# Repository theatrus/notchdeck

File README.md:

# NotchDeck

**NotchDeck One** is a BenchBits train controller project with USB HID and Bluetooth LE HID.
It supports our own Japanese-style **separate power lever and rotary brake**, or a
**combined mascon**. Each handle can use an AS5600 magnetic sensor or a Gray-code
contact cam. The goal is a driverless joystick with host-controlled lighting;
host/game compatibility has not yet been bench-tested.

## Current design: Rev G logic + Rev E button panel

| Assembly | Function | Provisional floorplan |
|---|---|---|
| [Logic / connectors](hardware/notchdeck-one/FLOORPLAN.md) | E73 nRF52840 module, USB/BLE, battery power, handle ports, Select/Start, two solenoids and buzzer | 115×90mm, four layers |
| [Button panel](hardware/notchdeck-buttons/README.md) | STM32G030, detachable 4×4 diode key matrix, 16 RGB LEDs | 86×120mm, two layers, 19mm key pitch |

A six-way 1mm FFC carries power, I²C and interrupt between boards. The selected cable
is Molex **0151670213** (DigiKey **WM13121-ND**); the panel guide records its reversed
connector numbering and remaining fit checks. The STM32G030 **C529330** was selected
from owned JLCPCB inventory.

The [actuator sheet](hardware/notchdeck-one/ACTUATORS.md) adds two PWM low-side
outputs, an active-buzzer output and 3.3V signals for an external 12V driver.
A TPS259461LRPWR electronic limiter protects the full battery input at 5.05A
nominal. The provisional target is two simultaneous 2A strikes of up to 100ms,
then lower PWM hold current. Use a protected ≥6A 1S pack for upstream shorts.
ACT_EN pauses charging during actuation; the PWM inputs default off.

Both hierarchical schematics are wired and pass strict ERC, complete net checks,
schematic/PCB parity and BOM audits. **Both PCBs are unrouted floorplans and are not
ready for fabrication.** The [hardware guide](hardware/README.md) tracks routing,
mechanical, power-budget and assembly work still required.

The nRF firmware builds against NCS v3.3.0, with host tests and six Rev C/D handle
profiles compiled in CI. **Panel firmware, main-board I²C integration and Rev G actuator control are
not implemented.** Keep loads disconnected when using old Rev C/D firmware.
Magnetic handles also require measured detent calibration. No production firmware,
bootloader integration or fabricated-controller validation is claimed.

## Handles and reports

Combined mode sends discrete notch values on HID **Y**: EB=`0x00`, N=`0x80`, P5=`0xFF`.
Separate-handle mode uses **Y=power, X=brake**, with brake priority and neutral
re-arming. Both magnetic and contact backends use absolute positions. See the
[handle interface](docs/06-handle-interfaces.md) for cam codes, calibration and
profiles, and the [own-build guide](docs/07-japanese-handle-build.md) for mechanisms
and the provisional panel layout.

## Checks and exports

Run from the repository root:

```sh
make -C firmware test             # host compiler only
make -C hardware verify           # KiCad 10 + Python with pcbnew
make -C hardware jlc              # separate logic and button assembly ZIPs
```

On Linux, pass `KICAD_PYTHON=python3` to hardware checks with KiCad's Python module
installed. The [hardware guide](hardware/README.md) covers setup and regeneration;
the [firmware guide](firmware/README.md) covers NCS builds and release commands.

Each hardware ZIP contains Gerbers, drill, BOM and pick-and-place (CPL) files.
Exports describe the current unfinished boards; exporting does not approve them
for manufacture. [Sourcing](docs/04-bom-sourcing.md) covers **five complete sets**:
213 installed parts and 44 JLCPCB codes per set, plus the separate cable. Stock
observations are dated snapshots, with private inventory retained outside Git.
The earlier Rev E parts order was placed; the Rev G actuator expansion still
needs a top-up for 20 sets plus 10% spares. See the sourcing guide.

[GitHub Actions](https://github.com/theatrus/notchdeck/actions/workflows/ci.yml)
publishes `notchdeck-boms` (both assembly BOMs) and `notchdeck-one-firmware`
(default nRF52840 DK bring-up UF2/HEX). Handle profiles are compile checks only;
there is no Rev E/F or STM32 image in those artifacts. CI checks floorplan DRC rules
and parity while allowing the documented unrouted connections.

## Documentation

| Guide | Contents |
|---|---|
| [Hardware](hardware/README.md) | KiCad projects, validation, manufacturing exports and open work |
| [Actuators](hardware/notchdeck-one/ACTUATORS.md) | Short protection, connectors, PWM limits and required firmware |
| [Firmware](firmware/README.md) | Build/test commands, CI artifacts and implementation status |
| [Architecture](docs/03-hardware-and-firmware-architecture.md) | Two-board design, buses, power and firmware responsibilities |
| [Sourcing](docs/04-bom-sourcing.md) | Assembly BOMs, five-set stock accounting and external parts |
| [Parts](hardware/PARTS.md) / [net plan](hardware/NETPLAN.md) | Exact selections, footprints, pad assignments and wiring |
| [Handle interfaces](docs/06-handle-interfaces.md) | Magnetic/Gray harnesses, codes, profiles and fault behavior |
| [Japanese-style handle build](docs/07-japanese-handle-build.md) | Own-build mechanics, provisional layout and cam targets |
| [Protocol](docs/02-emulation-protocol-spec.md) | HID reports, notch encoding and planned lighting features |
| [Firmware updates](docs/05-firmware-update.md) | Current artifacts, SWD access and proposed user-update path |
| [Research](docs/01-research-findings.md) | Original Zuiki/Densha de GO! protocol research and references |

## License

TBD; a project-wide license has not yet been selected. Third-party library sources
and licenses are recorded in [attributions](hardware/lib/ATTRIBUTIONS.md).

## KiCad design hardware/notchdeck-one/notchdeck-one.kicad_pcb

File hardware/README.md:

# NotchDeck hardware

**Rev G logic and Rev E panel are two wired KiCad 10 assemblies:** `notchdeck-one` is the logic/handle board; `notchdeck-buttons` is the detachable 4×4 key/RGB board. The button board uses an owned **STM32G030F6P6TR / C529330** to scan a diode matrix and drive RGB locally. A six-way 1mm FFC carries I²C, interrupt and power. Select/Start remain direct inputs on the main board, alongside Reset.

| Project | Provisional PCB | Electrical components | Nets / endpoints | Assembly parts |
|---|---|---:|---|---:|
| [Logic](notchdeck-one/FLOORPLAN.md) | 115×90mm, four layers | 130 | 94 / 409 | 129 |
| [Buttons](notchdeck-buttons/README.md) | 86×120mm, two layers; 19mm key pitch | 85 | 56 / 235 | 84 |

Both have zero native ERC errors/warnings, complete independent net contracts, and matching PCB pad nets, schematic UUIDs and sourcing properties. Both are **unrouted floorplans**, with no tracks/vias/planes. Native DRC has no rule or schematic-parity violations; 323 logic and 211 button connections remain unrouted. Neither is ready to fabricate.

Open `notchdeck-one/notchdeck-one.kicad_pro` and
`notchdeck-buttons/notchdeck-buttons.kicad_pro` in KiCad 10 to inspect the complete
projects, then open each project's root schematic or PCB from its project manager.
The root schematics link the child sheets; symbols/footprints use standard KiCad
libraries plus the shared project-local `lib/` directory.

Magnetic and Gray-coded power/brake or combined mascon interfaces remain electrically unchanged. See [handle interfaces](../docs/06-handle-interfaces.md). U9 separates the two AS5600 address-0x36 channels; MAX17048 remains on another bus. Remove both R37/R38 before using an external power/combined sensor on J10.

Rev G adds [two solenoids, an active buzzer and external PWM](notchdeck-one/ACTUATORS.md). The actuator feed uses electronic current limiting, with no disposable fuse. A protected ≥6A 1S pack is mandatory for upstream battery-lead/PCB shorts. Full battery input protection is set to 5.05A nominal, with a 4.3A operating budget and two provisional 2A/100ms strikes. ACT_EN pauses charging; PWM pulldowns default the loads off.

## Source of truth and build

Edit `scripts/<project>.schgen.py` and each project's `bom/jlcpcb-parts.json`, then generate with the schematic editors closed. `notchdeck_capture.py` supplies shared wire/port capture; `kschgen.py` handles native files. Keep editor changes in those manifests before forcing regeneration. The saved PCBs become the source of truth once placement/routing proceeds; the seed floorplan script refuses to overwrite routed boards.

```sh
# From hardware/; <project> is notchdeck-one or notchdeck-buttons.
KSCHGEN_FORCE=1 make gen-notchdeck-one gen-notchdeck-buttons
make verify                     # both boards: net/ERC, PCB parity and BOM audits
make render-notchdeck-one render-notchdeck-buttons
make docs                       # both boards' images and BOMs
make jlc                        # two separate Gerber/drill/BOM/CPL ZIPs
make jlc-notchdeck-buttons       # or export one PCB
```

Pick-and-place files are `<project>/jlcpcb/<project>-CPL.csv`; ZIPs are `<project>/<project>-jlcpcb.zip`. These commands export the current design, including unfinished floorplans; they do not constitute a manufacturing release. Review rotations in JLCPCB before ordering. Generated exports are ignored by Git. CI audits both projects; on Linux pass `KICAD_PYTHON=python3` with `pcbnew` installed. See [script guide](scripts/README.md).

Use `KICAD_CLI=/Applications/KiCad/KiCad.app/Contents/MacOS/kicad-cli` on macOS
if the executable is not on PATH; the Makefile's native export targets need it.
The default `KICAD_PYTHON` points to KiCad's bundled macOS Python. Headless Linux
also needs the standard symbol/footprint tables installed, as shown in
[CI setup](../.github/workflows/ci.yml). Rendering PNG sheets requires an SVG
converter listed in the script guide.

CI publishes both generated BOM CSVs as `notchdeck-boms`; it does not publish
assembly ZIPs or CPLs. `make verify` does not include native DRC: CI runs that
separately, rejects rule/parity violations and reports unrouted counts. Before
manufacturing, all unintended unconnected items must also be resolved.

## Sourcing and remaining work

[PARTS.md](PARTS.md) maps all **213 installed parts / 44 JLCPCB codes** per set. [Five-set stock](jlcpcb-five-set-stock.csv) combines both boards’ usage: dated public availability or owned stock covers the five-set requirement; new C3662776 has 110 displayed in stock, with order allocation still to confirm. Private inventory balances remain outside Git. [System BOM](system-bom.csv) adds one DigiKey Molex 0151670213 cable per set. The user placed the earlier Rev E parts order; the shared CSV was refreshed afterward. Rev G additions need a separate top-up, recorded locally in `~/Dropbox-elec/github/notchdeck-actuator-expansion-2026-10-04.csv`. Stock observations do not reserve parts. Handle mechanisms, external sensor carriers, cell, keycaps and enclosure are not yet a sourced kit.

- Implement panel MCU firmware and main I²C integration. Existing Rev C/D direct-GPIO button/RGB firmware does **not** operate this Rev E panel. The [panel guide](notchdeck-buttons/README.md) records pin functions, scan behavior, address and programming requirements.
- Implement Rev G actuator startup/strike/hold, instantaneous current-budget scheduling, undervoltage shutdown, fault latching and timeout handling. No safe actuator image exists yet. Select actual coils/buzzer and a protected pack; qualify short behavior and temperature rise.
- Finalize enclosure, cable fit/retention and tolerances, mounting and connector access. The FFC is nominally compatible; its guaranteed thickness tolerance is wider than the connector drawing. Sample-fit or supplier approval remains required.
- Validate E73 land pattern/antenna region and MAX17048 exposed pad. Review final CPL orientation and assembly eligibility.
- Resolve USB source/current/inrush and the existing 500mA charger setting. RGB is USB-only; a ≤250mA total panel return target is below the 0.5A FFC-contact rating, but still needs firmware enforcement and a whole-system power budget. Review LDO margins and battery choice.
- Finish decoupling placement, USB/ESD routing, reference planes and ground stitching; route and run final DRC/DFM/EMC checks. Magnetic detents need measured calibration; handle hardware and power/thermal behavior need bench testing.

Connectivity and catalog checks establish internal consistency, not complete electrical, mechanical or production validation. No ERC exclusions were added.

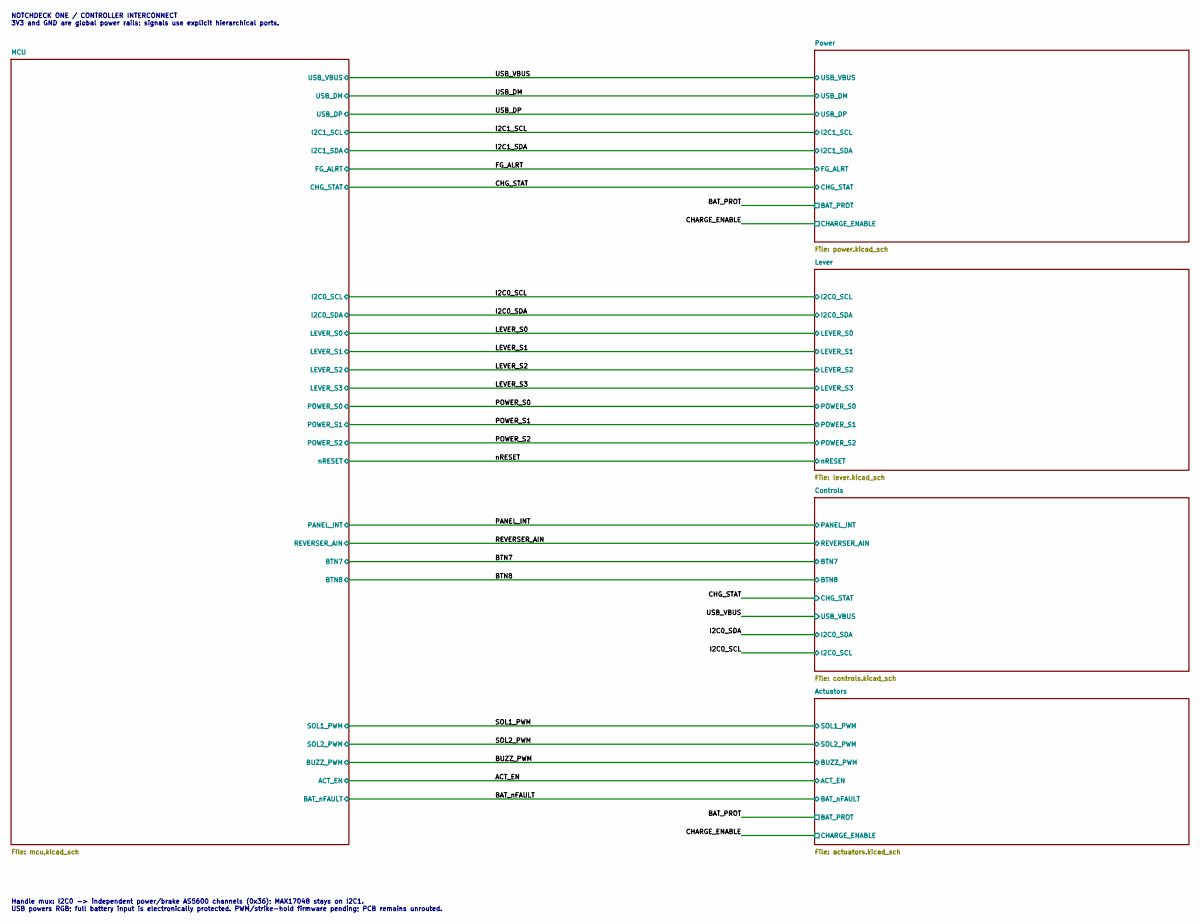
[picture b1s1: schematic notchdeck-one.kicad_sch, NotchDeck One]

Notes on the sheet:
NOTCHDECK ONE / CONTROLLER INTERCONNECT 3V3 and GND are global power rails; signals use explicit hierarchical ports.
Handle mux: I2C0 -> independent power/brake AS5600 channels (0x36); MAX17048 stays on I2C1. USB powers RGB; full battery input is electronically protected. PWM/strike-hold firmware pending; PCB remains unrouted.

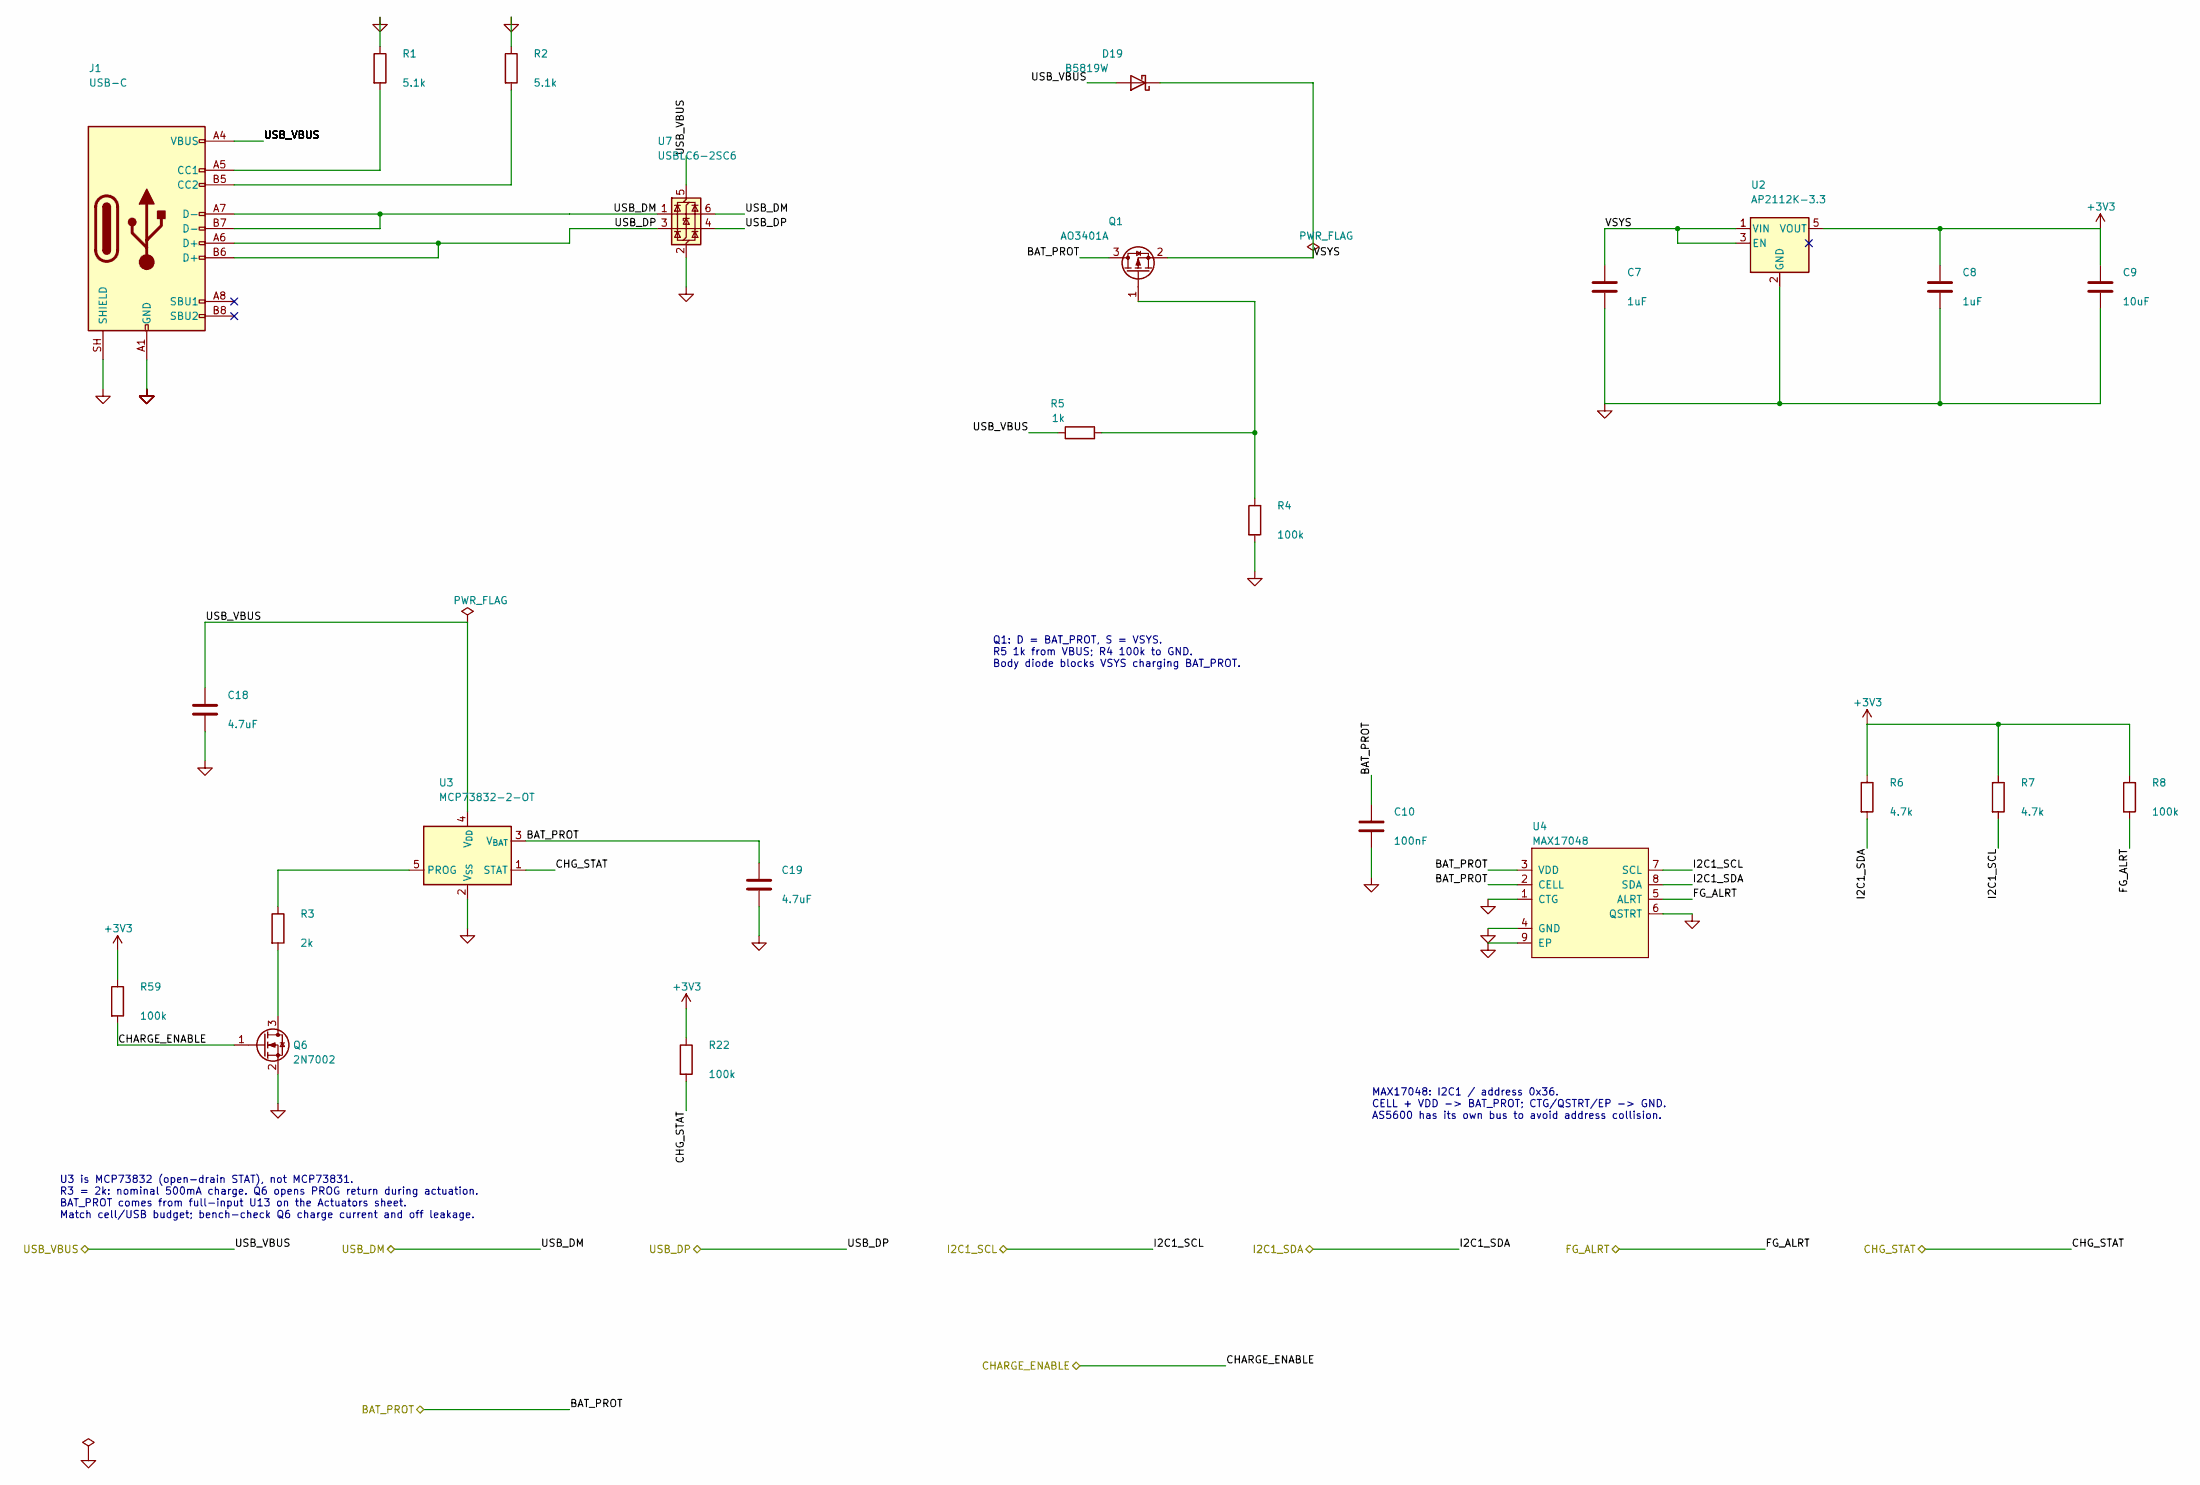
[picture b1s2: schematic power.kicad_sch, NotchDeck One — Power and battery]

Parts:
C7, C8: 1uF; C_0402_1005Metric; MPN CL05A105KA5NQNC; LCSC C52923
C9: 10uF; C_0805_2012Metric; MPN CL21A106KAYNNNE; LCSC C15850
C10: 100nF; C_0402_1005Metric; MPN CL05B104KO5NNNC; LCSC C1525
C18, C19: 4.7uF; C_0805_2012Metric; MPN CL21A475KAQNNNE; LCSC C1779
D19: B5819W; D_SOD-123; MPN B5819W SL; LCSC C8598
J1: USB-C; USB_C_Receptacle_HRO_TYPE-C-31-M-12; MPN TYPE-C-31-M-12; LCSC C165948
Q1: AO3401A; SOT-23; MPN AO3401A; LCSC C15127
Q6: 2N7002; SOT-23; MPN 2N7002; LCSC C8545
R1, R2: 5.1k; R_0402_1005Metric; MPN 0402WGF5101TCE; LCSC C25905
R3: 2k; R_0402_1005Metric; MPN 0402WGF2001TCE; LCSC C4109
R4, R8, R22, R59: 100k; R_0402_1005Metric; MPN 0402WGF1003TCE; LCSC C25741
R5: 1k; R_0402_1005Metric; MPN 0402WGF1001TCE; LCSC C11702
R6, R7: 4.7k; R_0402_1005Metric; MPN 0402WGF4701TCE; LCSC C25900
U2: AP2112K-3.3; SOT-23-5; MPN AP2112K-3.3TRG1; LCSC C51118
U3: MCP73832-2-OT; SOT-23-5; MPN MCP73832T-2ACI/OT; LCSC C38066
U4: MAX17048; TDFN-8-1EP_2x2mm_P0.5mm_EP0.8x1.2mm; MPN MAX17048G+T10; LCSC C2682616
U7: USBLC6-2SC6; SOT-23-6; MPN USBLC6-2SC6; LCSC C7519

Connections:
+3V3: C8.1, C9.1, R6.1, R7.1, R8.1, R22.1, R59.1, U2.5 (VOUT); also elsewhere on the board
/BAT_PROT: C10.1, C19.1, Q1.3 (D), U3.3 (V_{BAT}), U4.2 (CELL), U4.3 (VDD); also elsewhere on the board
/CHARGE_ENABLE: Q6.1 (G), R59.2; also elsewhere on the board
/CHG_STAT: R22.2, U3.1 (STAT); also elsewhere on the board
/FG_ALRT: R8.2, U4.5 (ALRT); also elsewhere on the board
/I2C1_SCL: R7.2, U4.7 (SCL); also elsewhere on the board
/I2C1_SDA: R6.2, U4.8 (SDA); also elsewhere on the board
/USB_DM: J1.A7 (D-), J1.B7 (D-), U7.1 (I/O1), U7.6 (I/O1); also elsewhere on the board
/USB_DP: J1.A6 (D+), J1.B6 (D+), U7.3 (I/O2), U7.4 (I/O2); also elsewhere on the board
unnamed: J1.A5 (CC1), R1.2
unnamed: J1.B5 (CC2), R2.2
unnamed: Q1.1 (G), R4.1, R5.2
unnamed: Q6.3 (D), R3.2
unnamed: R3.1, U3.5 (PROG)

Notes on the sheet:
Q1: D = BAT_PROT, S = VSYS. R5 1k from VBUS; R4 100k to GND. Body diode blocks VSYS charging BAT_PROT.
U3 is MCP73832 (open-drain STAT), not MCP73831. R3 = 2k: nominal 500mA charge. Q6 opens PROG return during actuation. BAT_PROT comes from full-input U13 on the Actuators sheet. Match cell/USB budget; bench-check Q6 charge current and off leakage.
MAX17048: I2C1 / address 0x36. CELL + VDD -> BAT_PROT; CTG/QSTRT/EP -> GND. AS5600 has its own bus to avoid address collision.

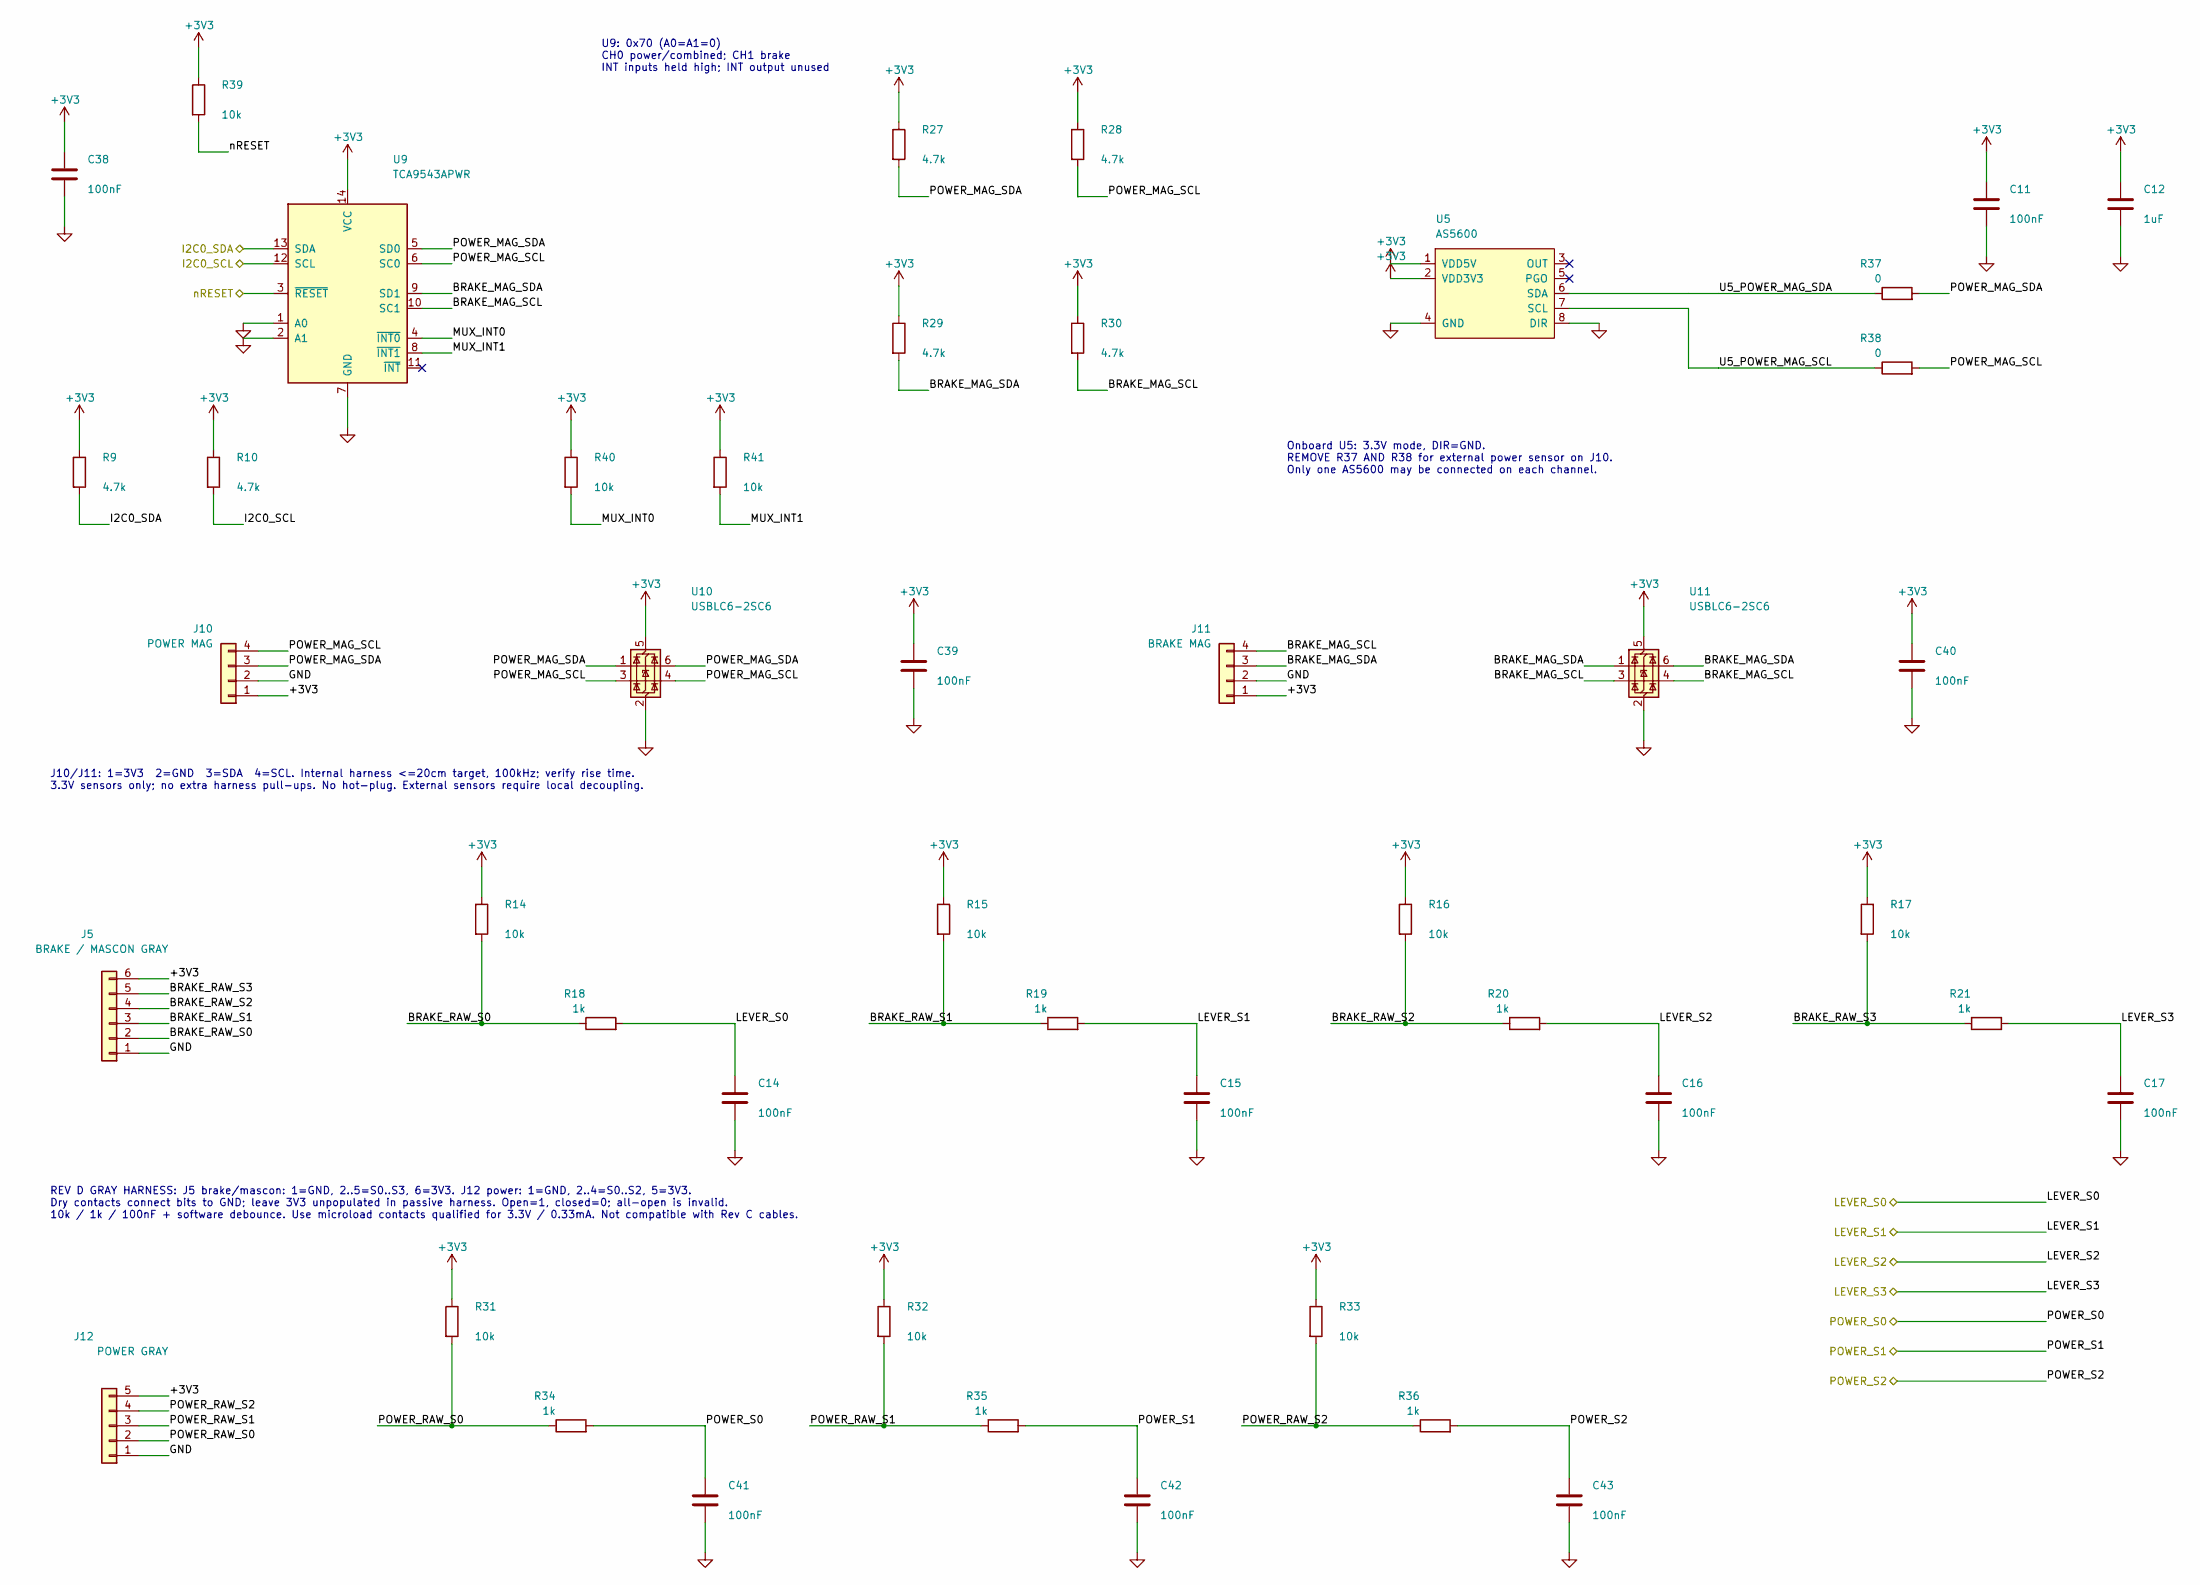
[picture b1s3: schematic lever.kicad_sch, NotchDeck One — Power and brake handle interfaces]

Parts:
C11, C14, C15, C16, C17, C38, C39, C40, C41, C42, C43: 100nF; C_0402_1005Metric; MPN CL05B104KO5NNNC; LCSC C1525
C12: 1uF; C_0402_1005Metric; MPN CL05A105KA5NQNC; LCSC C52923
J5: BRAKE / MASCON GRAY; JST_PH_S6B-PH-SM4-TB_1x06-1MP_P2.00mm_Horizontal; MPN S6B-PH-SM4-TB(LF)(SN); LCSC C265405
J10: POWER MAG; JST_PH_S4B-PH-SM4-TB_1x04-1MP_P2.00mm_Horizontal; MPN S4B-PH-SM4-TB(LF)(SN); LCSC C265102
J11: BRAKE MAG; JST_PH_S4B-PH-SM4-TB_1x04-1MP_P2.00mm_Horizontal; MPN S4B-PH-SM4-TB(LF)(SN); LCSC C265102
J12: POWER GRAY; JST_PH_S5B-PH-SM4-TB_1x05-1MP_P2.00mm_Horizontal; MPN S5B-PH-SM4-TB(LF)(SN); LCSC C265104
R9, R10, R27, R28, R29, R30: 4.7k; R_0402_1005Metric; MPN 0402WGF4701TCE; LCSC C25900
R14, R15, R16, R17, R31, R32, R33, R39, R40, R41: 10k; R_0402_1005Metric; MPN 0402WGF1002TCE; LCSC C25744
R18, R19, R20, R21, R34, R35, R36: 1k; R_0402_1005Metric; MPN 0402WGF1001TCE; LCSC C11702
R37, R38: 0; R_0603_1608Metric; MPN 0603WAF0000T5E; LCSC C21189
U5: AS5600; SOIC-8_3.9x4.9mm_P1.27mm; MPN AS5600-ASOT; LCSC C499458
U9: TCA9543APWR; TSSOP-14_4.4x5mm_P0.65mm; MPN TCA9543APWR; LCSC C2653307
U10, U11: USBLC6-2SC6; SOT-23-6; MPN USBLC6-2SC6; LCSC C7519

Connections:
+3V3: C11.1, C12.1, C38.1, C39.1, C40.1, J5.6, J10.1, J11.1, J12.5, R9.1, R10.1, R14.1, R15.1, R16.1, R17.1, R27.1, R28.1, R29.1, R30.1, R31.1, R32.1, R33.1, R39.1, R40.1, R41.1, U5.1 (VDD5V), U5.2 (VDD3V3), U9.14 (VCC), U10.5 (VBUS), U11.5 (VBUS); also elsewhere on the board
/I2C0_SCL: R10.2, U9.12 (SCL); also elsewhere on the board
/I2C0_SDA: R9.2, U9.13 (SDA); also elsewhere on the board
/LEVER_S0: C14.1, R18.2; also elsewhere on the board
/LEVER_S1: C15.1, R19.2; also elsewhere on the board
/LEVER_S2: C16.1, R20.2; also elsewhere on the board
/LEVER_S3: C17.1, R21.2; also elsewhere on the board
/Lever/BRAKE_MAG_SCL: J11.4, R30.2, U9.10 (SC1), U11.3 (I/O2), U11.4 (I/O2)
/Lever/BRAKE_MAG_SDA: J11.3, R29.2, U9.9 (SD1), U11.1 (I/O1), U11.6 (I/O1)
/Lever/BRAKE_RAW_S0: J5.2, R14.2, R18.1
/Lever/BRAKE_RAW_S1: J5.3, R15.2, R19.1
/Lever/BRAKE_RAW_S2: J5.4, R16.2, R20.1
/Lever/BRAKE_RAW_S3: J5.5, R17.2, R21.1
/Lever/MUX_INT0: R40.2, U9.4 (~INT0)
/Lever/MUX_INT1: R41.2, U9.8 (~INT1)
/Lever/POWER_MAG_SCL: J10.4, R28.2, R38.2, U9.6 (SC0), U10.3 (I/O2), U10.4 (I/O2)
/Lever/POWER_MAG_SDA: J10.3, R27.2, R37.2, U9.5 (SD0), U10.1 (I/O1), U10.6 (I/O1)
/Lever/POWER_RAW_S0: J12.2, R31.2, R34.1
/Lever/POWER_RAW_S1: J12.3, R32.2, R35.1
/Lever/POWER_RAW_S2: J12.4, R33.2, R36.1
/Lever/U5_POWER_MAG_SCL: R38.1, U5.7 (SCL)
/Lever/U5_POWER_MAG_SDA: R37.1, U5.6 (SDA)
/POWER_S0: C41.1, R34.2; also elsewhere on the board
/POWER_S1: C42.1, R35.2; also elsewhere on the board
/POWER_S2: C43.1, R36.2; also elsewhere on the board
/nRESET: R39.2, U9.3 (~RESET); also elsewhere on the board

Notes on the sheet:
U9: 0x70 (A0=A1=0) CH0 power/combined; CH1 brake INT inputs held high; INT output unused
Onboard U5: 3.3V mode, DIR=GND. REMOVE R37 AND R38 for external power sensor on J10. Only one AS5600 may be connected on each channel.
J10/J11: 1=3V3 2=GND 3=SDA 4=SCL. Internal harness <=20cm target, 100kHz; verify rise time. 3.3V sensors only; no extra harness pull-ups. No hot-plug. External sensors require local decoupling.
REV D GRAY HARNESS: J5 brake/mascon: 1=GND, 2..5=S0..S3, 6=3V3. J12 power: 1=GND, 2..4=S0..S2, 5=3V3. Dry contacts connect bits to GND; leave 3V3 unpopulated in passive harness. Open=1, closed=0; all-open is invalid. 10k / 1k / 100nF + software debounce. Use microload contacts qualified for 3.3V / 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

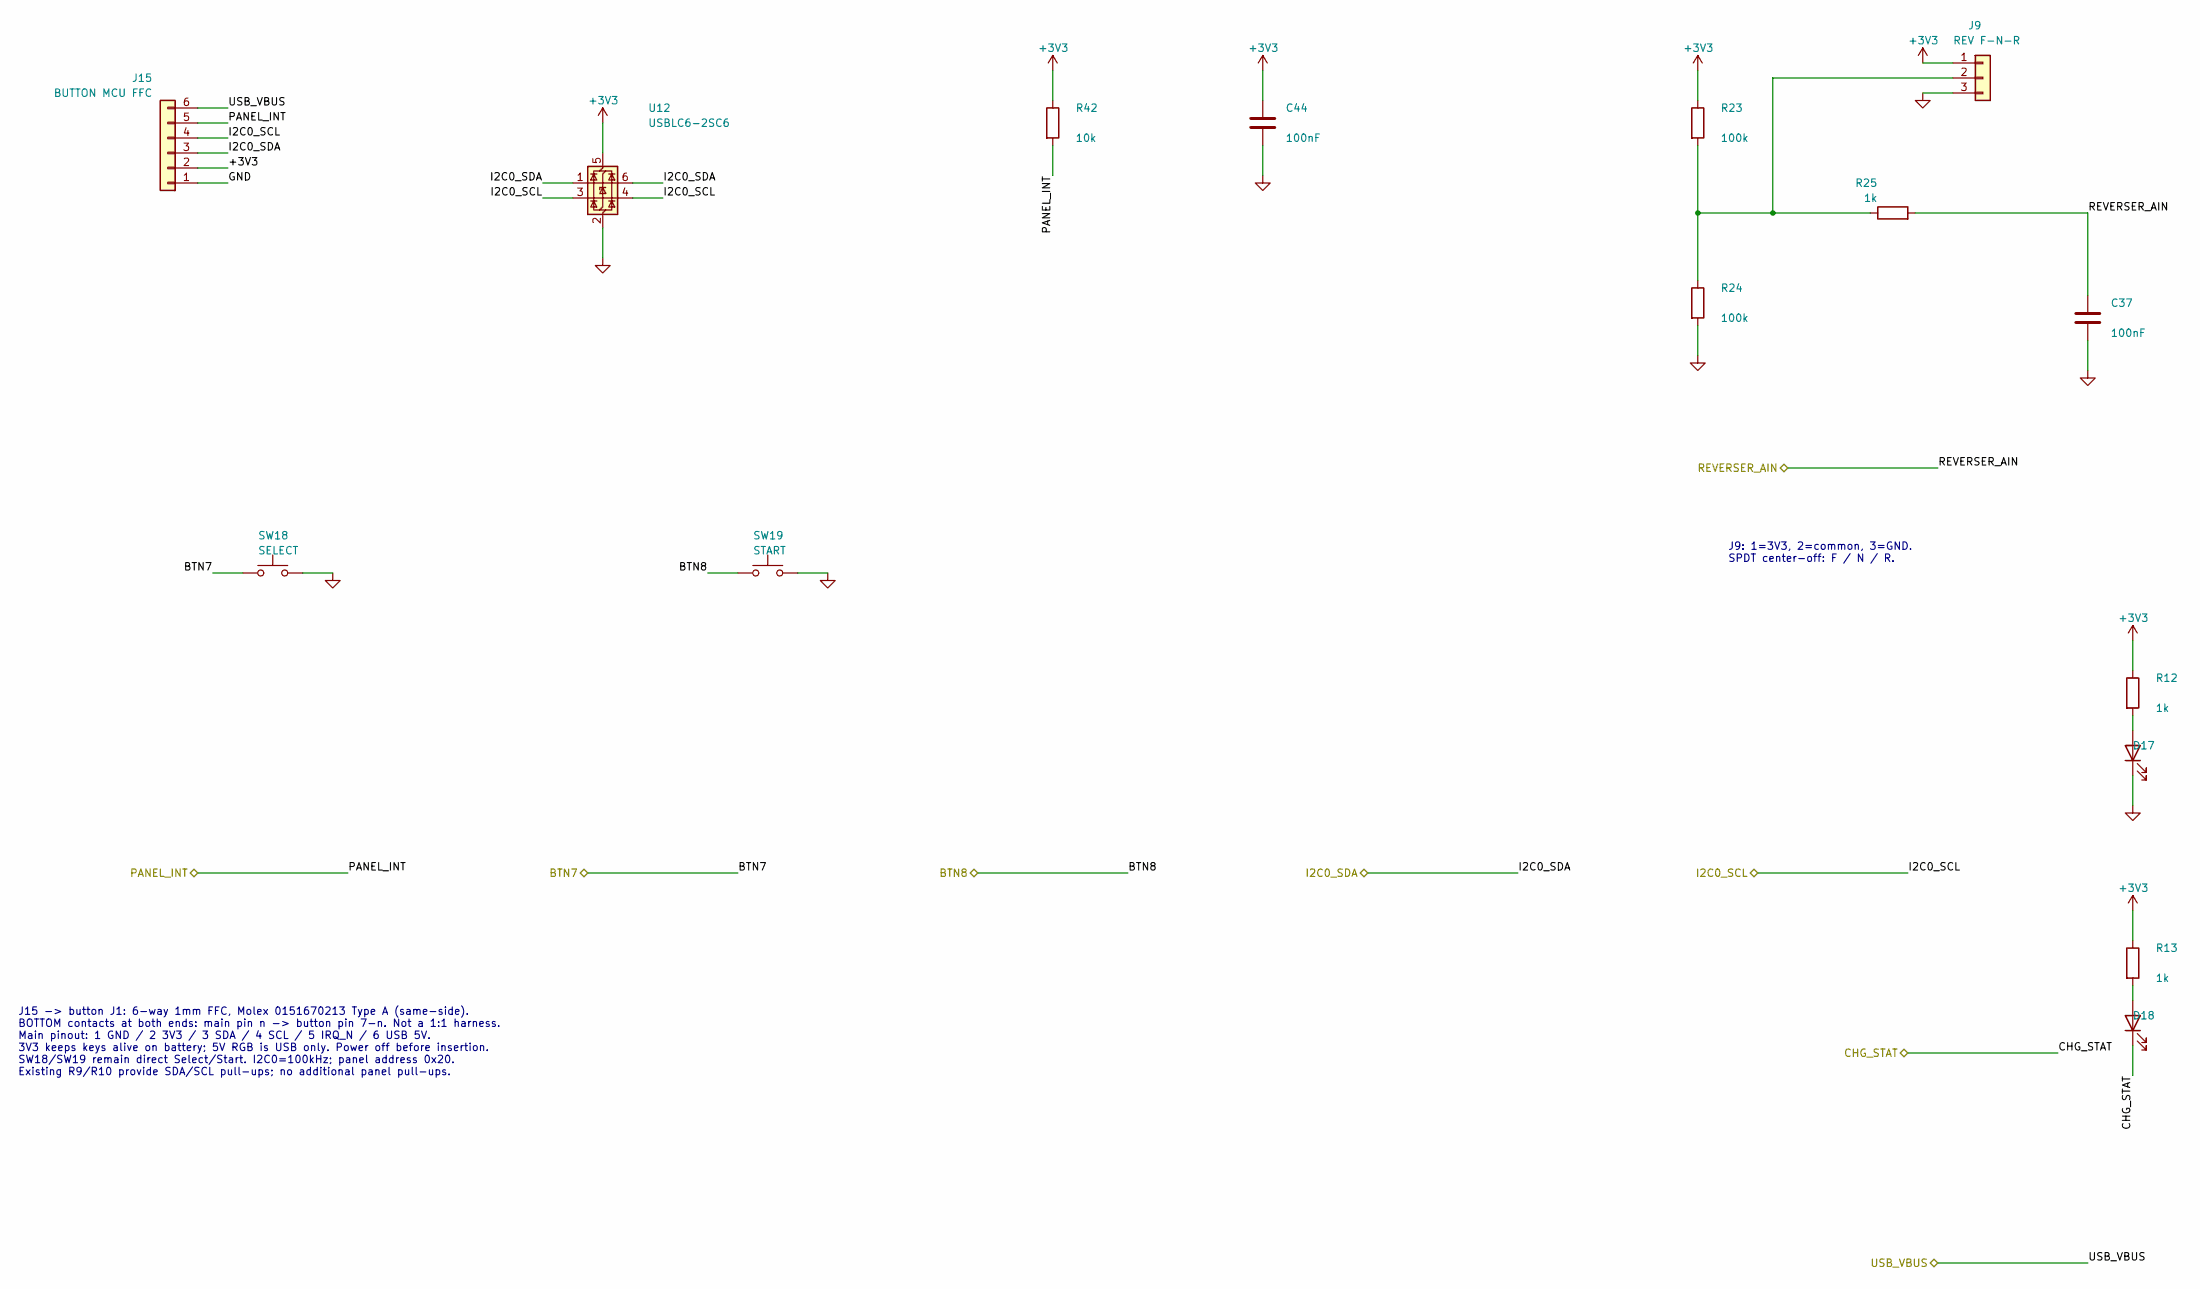
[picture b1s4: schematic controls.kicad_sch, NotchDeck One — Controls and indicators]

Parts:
C37, C44: 100nF; C_0402_1005Metric; MPN CL05B104KO5NNNC; LCSC C1525
D17: LED; LED_0603_1608Metric; MPN XL-1608SYGC-06; LCSC C965805
D18: LED; LED_0603_1608Metric; MPN KT-0603R; LCSC C2286
J9: REV F-N-R; JST_PH_S3B-PH-SM4-TB_1x03-1MP_P2.00mm_Horizontal; MPN S3B-PH-SM4-TB(LF)(SN); LCSC C265101
J15: BUTTON MCU FFC; JUSHUO_AFA07-S06FCA-00_1x6-1MP_P1.0mm_Horizontal; MPN AFA07-S06FCA-00; LCSC C262712
R12, R13, R25: 1k; R_0402_1005Metric; MPN 0402WGF1001TCE; LCSC C11702
R23, R24: 100k; R_0402_1005Metric; MPN 0402WGF1003TCE; LCSC C25741
R42: 10k; R_0402_1005Metric; MPN 0402WGF1002TCE; LCSC C25744
SW18: SELECT; SW_Push_1P1T_XKB_TS-1187A; MPN TS-1187A-B-A-B; LCSC C318884
SW19: START; SW_Push_1P1T_XKB_TS-1187A; MPN TS-1187A-B-A-B; LCSC C318884
U12: USBLC6-2SC6; SOT-23-6; MPN USBLC6-2SC6; LCSC C7519

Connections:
+3V3: C44.1, J9.1, J15.2, R12.1, R13.1, R23.1, R42.1, U12.5 (VBUS); also elsewhere on the board
/BTN7: SW18.1; also elsewhere on the board
/BTN8: SW19.1; also elsewhere on the board
/CHG_STAT: D18.1 (K); also elsewhere on the board
/I2C0_SCL: J15.4, U12.3 (I/O2), U12.4 (I/O2); also elsewhere on the board
/I2C0_SDA: J15.3, U12.1 (I/O1), U12.6 (I/O1); also elsewhere on the board
/PANEL_INT: J15.5, R42.2; also elsewhere on the board
/REVERSER_AIN: C37.1, R25.2; also elsewhere on the board
unnamed: D17.2 (A), R12.2
unnamed: D18.2 (A), R13.2
unnamed: J9.2, R23.2, R24.1, R25.1

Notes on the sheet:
J15 -> button J1: 6-way 1mm FFC, Molex 0151670213 Type A (same-side). BOTTOM contacts at both ends: main pin n -> button pin 7-n. Not a 1:1 harness. Main pinout: 1 GND / 2 3V3 / 3 SDA / 4 SCL / 5 IRQ_N / 6 USB 5V. 3V3 keeps keys alive on battery; 5V RGB is USB only. Power off before insertion. SW18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
J9: 1=3V3, 2=common, 3=GND. SPDT center-off: F / N / R.
